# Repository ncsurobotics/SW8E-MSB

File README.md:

# SW8E-MSB
Manipulation Systems Board supporting droppers, torpedo launchers, and grabber
=======
# SW9E-ManipulationSystemsBoard

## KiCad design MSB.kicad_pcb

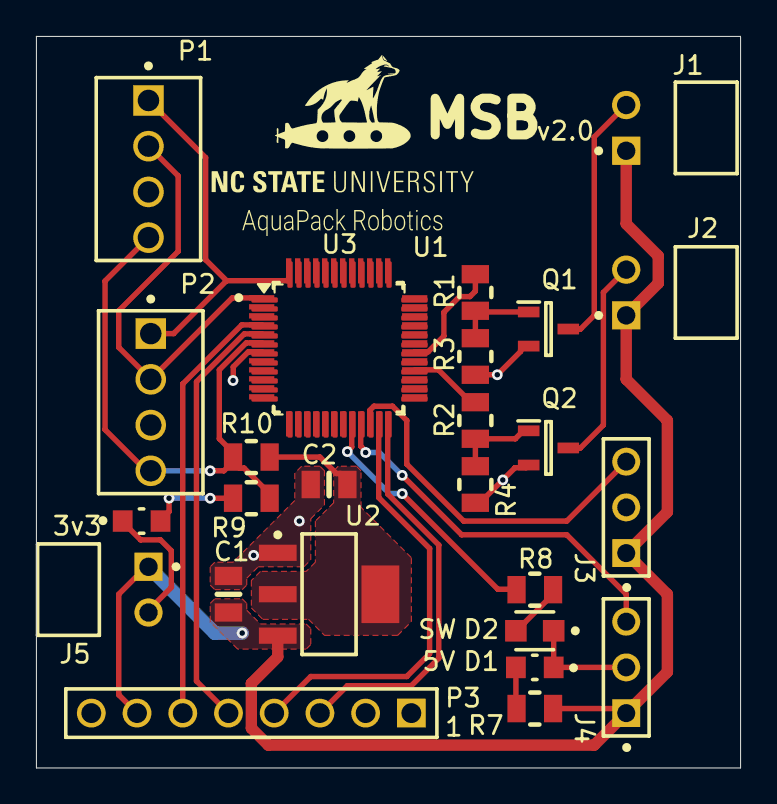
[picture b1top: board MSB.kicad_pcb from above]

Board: 2 copper layers, 39.1 x 40.6 mm, 26 parts (0 on the bottom side), 16 nets.

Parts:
C1: 100pF; SMD-0805C
C2: 10µF; SMD-0805C
D1, D3: 1.9V; FP-150080SS75000-MFG
D2: 2.2V; FP-LTST-C171GKT-MFG
J1, J2, J5: 22-05-3021; FP-22-05-3021-MFG
J3, J4: 90120-0763; FP-90120-0763-MFG
P1, P2: 22-27-2041; MOLX-22-27-2041_V
P3: 61300811121
Q1, Q2: FDN5632N-F085; SOT95P237X122-3N
R1, R2: 200; SMD-0805-RES
R3, R4: 10k; SMD-0805-RES
R7: 309; SMD-0805-RES
R8: 76.8; SMD-0805-RES
R9: 140; SMD-0805-RES
R10: 0.0; SMD-0805-RES
U1: MSP430FR2355TPTR; FP-PT0048A-MFG
U2: LD1117S33TR; SOT-223_L
U3: STM32L051C6Tx; LQFP-48_7x7mm_P0.5mm

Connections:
+3V3: P1.4, P2.4, R9.2, R10.2, U1.6 (DVCC)
+5: C1.1, J1.1, J2.1, J3.1, J3.3, J4.1, J5.1, P3.4, P3.7, R7.2, U2.3 (VIN), U3.15 (PA5), U3.30 (PA9)
/DROP1_CTRL: R1.1, U1.30 (P2.0/TB1.1/COMP0.O), U3.17 (PA7)
/DROP2_CTRL: R2.1, U1.28 (P2.2/TB1CLK), U3.16 (PA6)
/SCL: P1.1, P2.1, U1.48 (P1.3/UCB0SOMI/UCB0SCL/OA0+/A3), U3.26 (PB13)
/SDA: P1.2, P2.2, U1.1 (P1.2/UCB0SIMO/UCB0SDA/TB0TRG/OA0-/A2/Ve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), U3.27 (PB14)
/SERVO2_CTRL: J4.3, U1.21 (P6.1/TB3.2), U3.38 (PA15)
GND: C1.2, C2.2, D1.1 (C), D2.1 (C), D3.1 (C), J3.2, J4.2, J5.2, P1.3, P2.3, P3.8, Q1.2 (S), Q2.2 (S), R3.1, R4.1, U1.7 (DVSS), U2.1 (GND), U3.23 (VSS), U3.35 (VSS), U3.47 (VSS)
unnamed: C2.1, R10.1, U2.2 (VOUT), U2.4 (VOUT)
unnamed: D1.2 (A), R7.1
unnamed: D2.2 (A), R8.2
unnamed: D3.2 (A), R9.1
unnamed: J1.2, Q1.3 (D)
unnamed: Q1.1 (G), R1.2, R3.2
unnamed: J2.2, Q2.3 (D)
unnamed: Q2.1 (G), R2.2, R4.2

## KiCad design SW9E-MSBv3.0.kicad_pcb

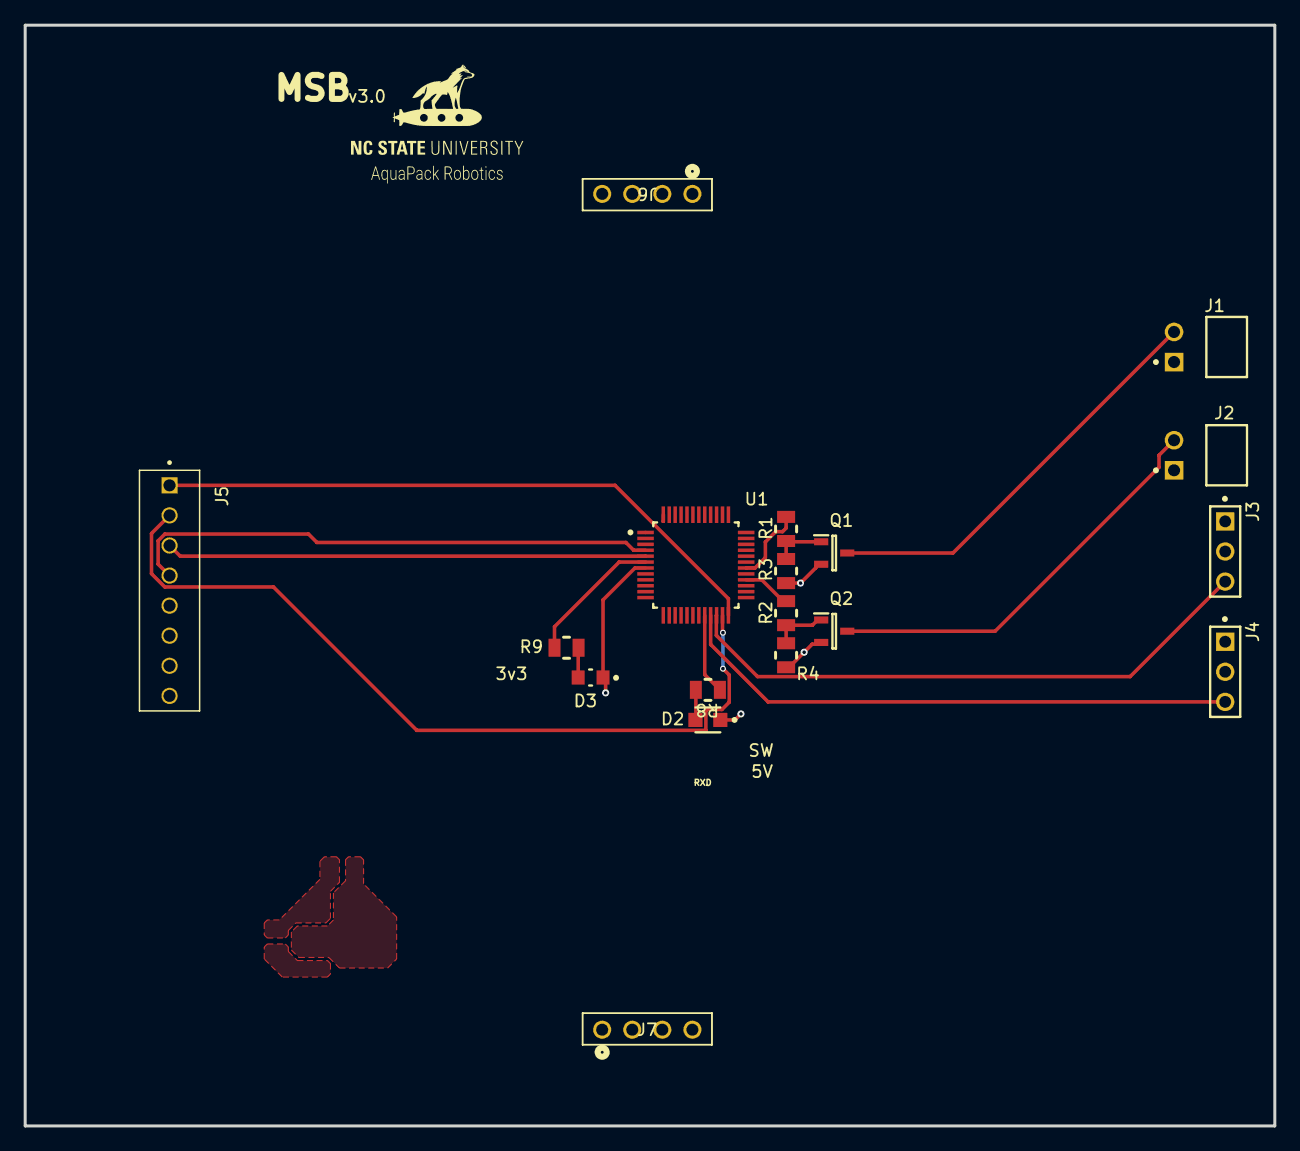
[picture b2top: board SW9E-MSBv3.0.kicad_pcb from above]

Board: 2 copper layers, 105.5 x 93.0 mm, 18 parts (0 on the bottom side), 20 nets.

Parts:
D2: 2.2V; FP-LTST-C171GKT-MFG
D3: 1.9V; FP-150080SS75000-MFG
J1, J2: 22-05-3021; FP-22-05-3021-MFG
J3, J4: 90120-0763; FP-90120-0763-MFG
J5: 640453-8; TE_640453-8
J6, J7: SSW-104-03-F-S; CON4_1X4_TU_SSQ
Q1, Q2: FDN5632N-F085; SOT95P237X122-3N
R1, R2: 200; SMD-0805-RES
R3, R4: 10k; SMD-0805-RES
R8: 76.8; SMD-0805-RES
R9: 140; SMD-0805-RES
U1: MSP430FR2355TPTR; FP-PT0048A-MFG

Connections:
+3.3V: J6.2, R9.2, U1.6 (DVCC)
+5V: J1.1, J2.1, J3.1, J4.1, J5.5, J6.3
/DROP1_CTRL: R1.1, U1.30 (P2.0/TB1.1/COMP0.O)
/DROP2_CTRL: R2.1, U1.28 (P2.2/TB1CLK)
/RST: J5.3, U1.5 (~RST/NMI/SBWTDIO)
/RXD: J5.1, U1.24 (P4.2/UCA1RXD/UCA1SOMI/~UCA1RXD)
/SCL: J7.1, U1.48 (P1.3/UCB0SOMI/UCB0SCL/OA0+/A3)
/SDA: J7.2, U1.1 (P1.2/UCB0SIMO/UCB0SDA/TB0TRG/OA0-/A2/Ve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)
/SERVO1_CTRL: J3.3, U1.22 (P6.0/TB3.1)
/SERVO2_CTRL: J4.3, U1.21 (P6.1/TB3.2)
/TST: J5.4, U1.4 (TEST/SBWTCK)
/TXD: J5.2, U1.23 (P4.3/UCA1TXD/UCA1SIMO/~UCA1TXD)
GND: D2.1 (C), D3.1 (C), J3.2, J4.2, J5.6, J6.1, Q1.2 (S), Q2.2 (S), R3.1, R4.1, U1.7 (DVSS)
unnamed: D2.2 (A), R8.2
unnamed: D3.2 (A), R9.1
unnamed: J1.2, Q1.3 (D)
unnamed: Q1.1 (G), R1.2, R3.2
unnamed: J2.2, Q2.3 (D)
unnamed: Q2.1 (G), R2.2, R4.2
unnamed: R8.1, U1.20 (P6.2/TB3.3)

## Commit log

2022-10-27 Initialized project and selected components, some basic layout
2022-11-01 Swapped NMOS, added duplicate servo and dropper hardware, initial layout
2022-11-03 Initial routing, added logos
2022-11-22 Swapped pours with cutouts to remove thermal relief
2023-03-21 Set up parameters for BOM
2023-03-21 Added BOM
2023-03-21 Added indicator LEDs and silk
2023-03-21 Removed 16.5ohm electromagnet resistors
2023-03-28 Imported MSB to KiCad
2023-06-05 Add license file
2023-07-04 Fix footprint linking and logos
2023-07-04 Fix polygons, silkscreen, and other DRC issues
2023-07-04 Cleanup sumbol field table
2024-02-06 Add gitignore
2024-02-22 Stuff
2025-02-11 Changed MSP430 to STM32
2025-03-26 Update STM32
2025-04-16 potential solution for stm32, updated stm32 schematic
2025-04-16 removed msp430 and moved stm32, disconnected swdio and swclk in subsheet
2025-04-16 updated schematic again, moved SWDIO and SWCLK out (not connected)
